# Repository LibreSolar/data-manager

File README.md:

# Data Manager for Libre Solar devices

 Prototype built, development and testing ongoing (especially firmware).

Schematic: [PDF file](data-manager.pdf)

Firmware repository: [LibreSolar/data-manager-firmware](https://github.com/LibreSolar/data-manager-firmware)

## Features

- ESP32 WROOM board for WiFi and Bluetooth connection
- USB Micro-B power supply and debug serial
- microSD card slot
- LS.one interface (UART serial)
- LS.bus interface (CAN)
- Suitable housing: Hammond Mfg. 1591XXAFLBK

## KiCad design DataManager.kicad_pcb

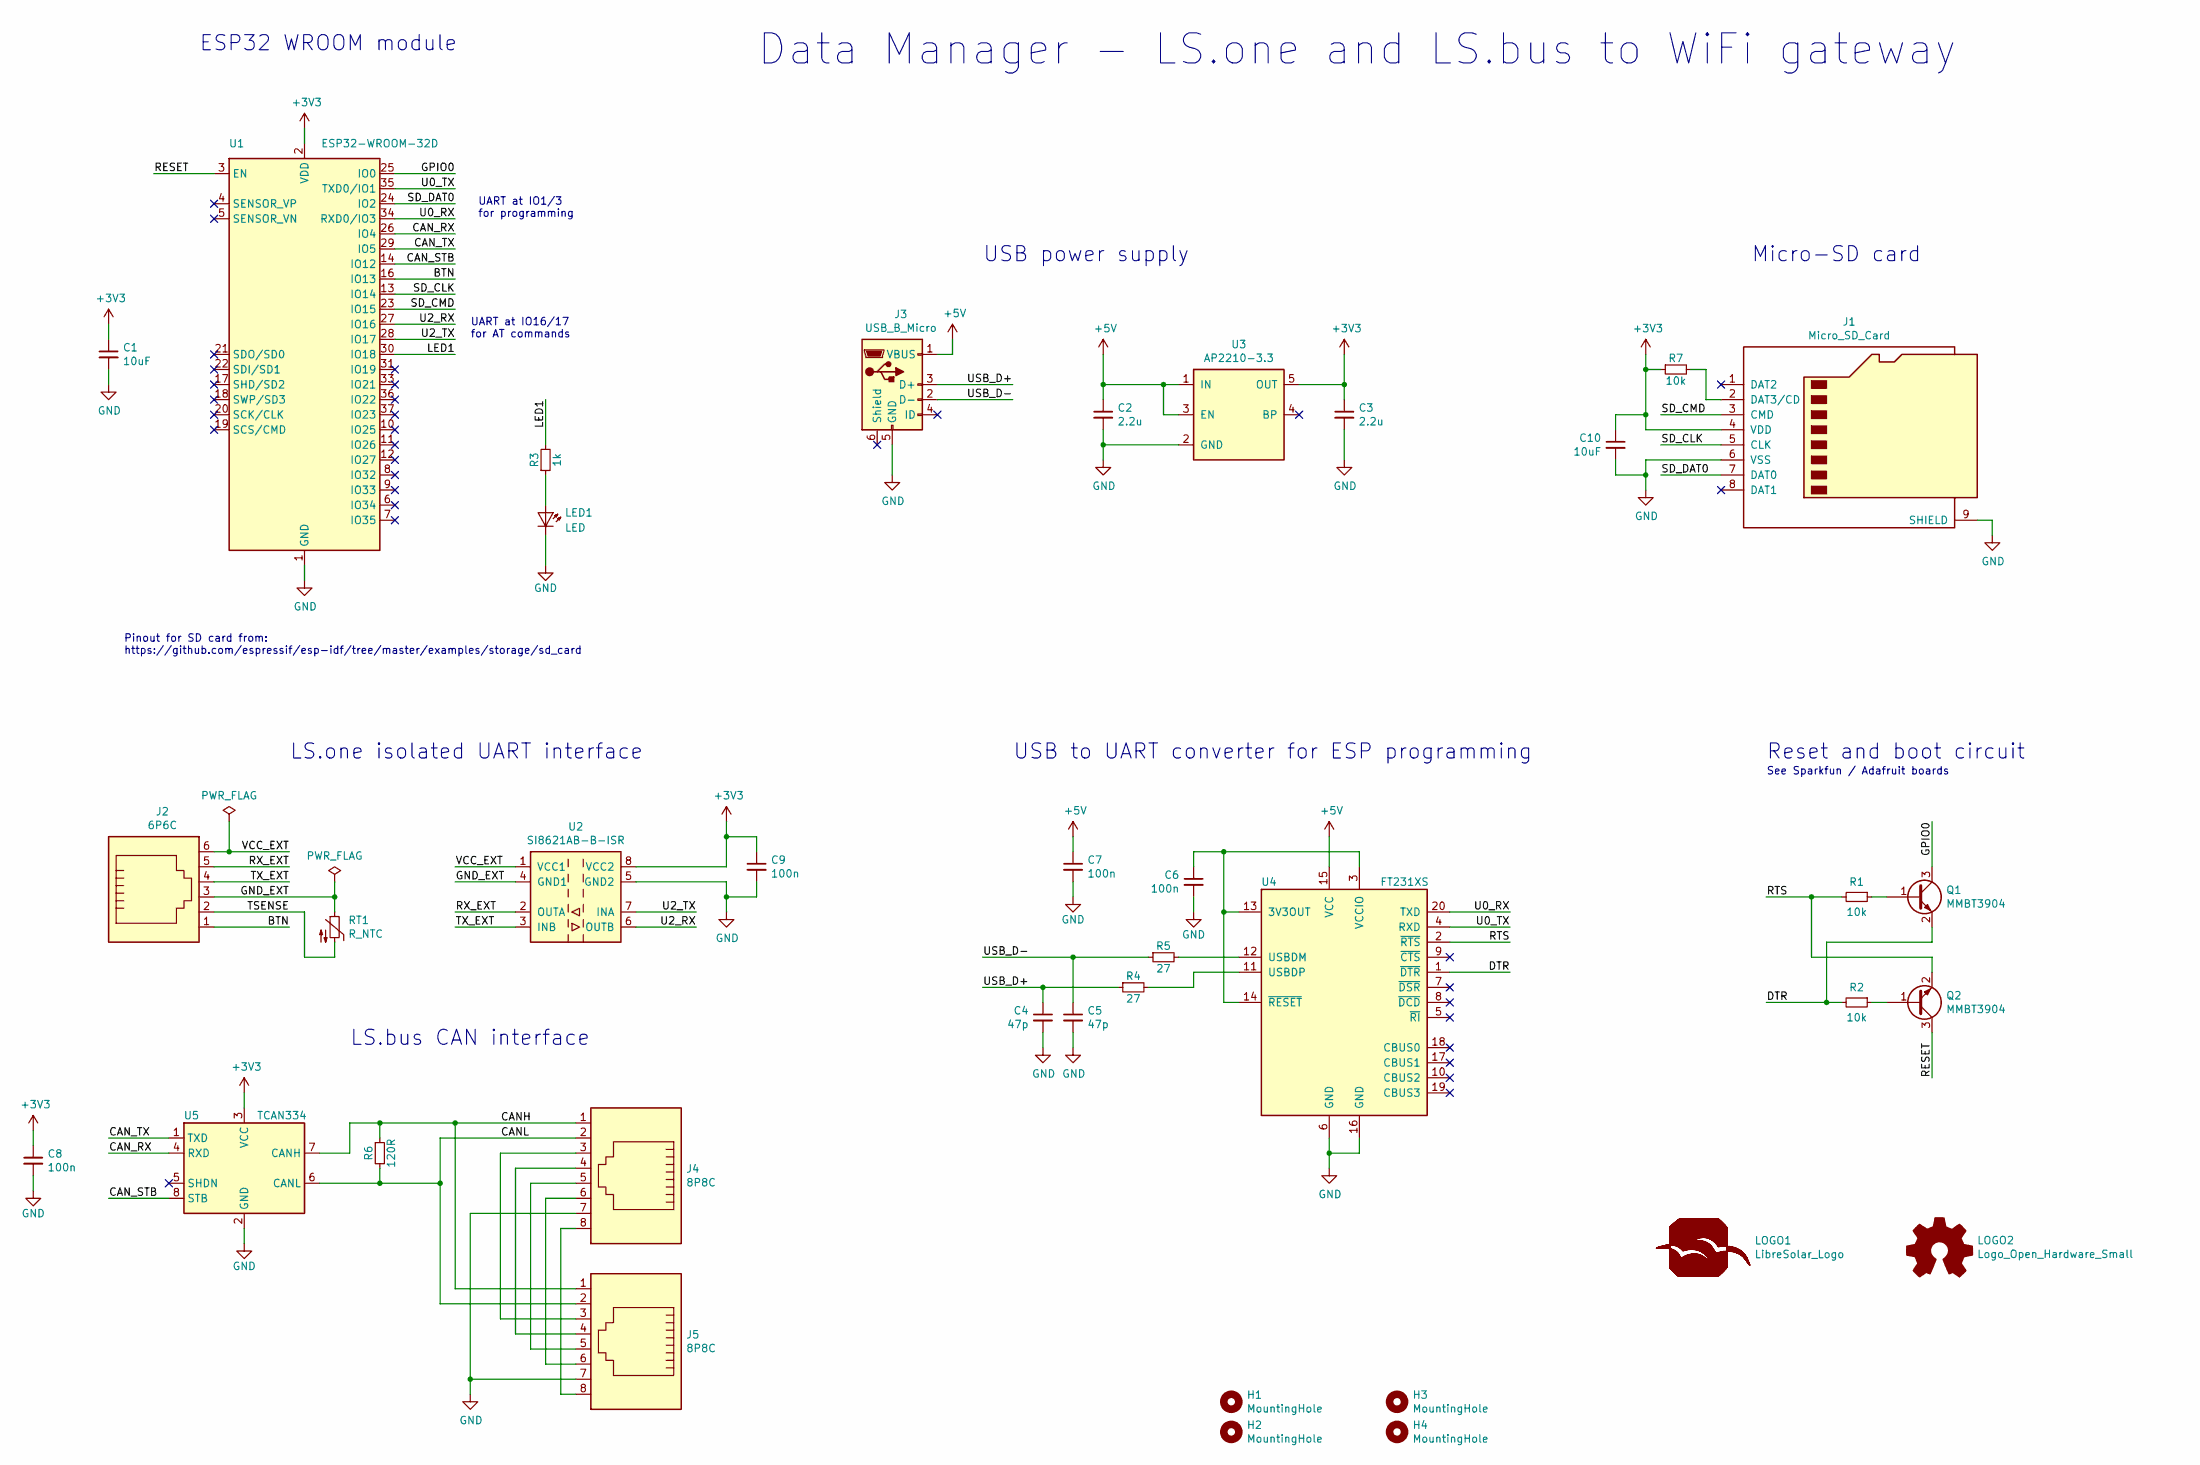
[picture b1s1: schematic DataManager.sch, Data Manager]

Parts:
C1, C10: 10uF; C_0805_2012; PartNumber GRM21BR61C106KE15L
C2, C3: 2.2u; C_0603_1608
C4, C5: 47p; C_0603_1608
C6, C7, C8, C9: 100n; C_0603_1608
H1, H2, H3, H4: MountingHole; MountingHole_2.5mm
J1: Micro_SD_Card; microSD_HC_Hirose_DM3D-SF; PartNumber DM3D-SF
J2: 6P6C; RJ12_RJ25_6P6C_Amphenol_54601; PartNumber 54601-906WPLF
J3: USB_B_Micro; USB_Micro-B_10103594-0001LF
J4, J5: 8P8C; RJ45_8P8C
LED1: LED; LED_0603_1608Metric
LOGO1: LibreSolar_Logo; LIBRESOLAR_LOGO
LOGO2: Logo_Open_Hardware_Small; OSHW-Logo_5.7x6mm_SilkScreen
Q1, Q2: MMBT3904; SOT-23
R1, R2, R7: 10k; R_0603_1608; PartNumber RC0603FR-0710KL
R3: 1k; R_0603_1608; PartNumber RC0603FR-071KL
R4, R5: 27; R_0603_1608; PartNumber RC0603FR-0727RL
R6: 120R; R_1206_3216; PartNumber RC1206FR-07120RL
RT1: R_NTC; R_0603_1608
U1: ESP32-WROOM-32D; ESP32-WROOM-32
U2: SI8621AB-B-ISR; SOIC-8_3.9x4.9mm_P1.27mm
U3: AP2210-3.3; SOT-23-5
U4: FT231XS; SSOP-20_3.9x8.7mm_P0.635mm
U5: TCAN334; SOIC-8_3.9x4.9mm_Pitch1.27mm

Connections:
+3V3: C1.1, C3.1, C8.1, C9.1, C10.1, J1.4 (VDD), R7.1, U1.2 (VDD), U2.8 (VCC2), U3.5 (OUT), U5.3 (VCC)
+5V: C2.1, C7.1, J3.1 (VBUS), U3.1 (IN), U3.3 (EN), U4.15 (VCC)
/BTN: J2.1, U1.16 (IO13)
/CANH: J4.1, J5.1, R6.1, U5.7 (CANH)
/CANL: J4.2, J5.2, R6.2, U5.6 (CANL)
/CAN_RX: U1.26 (IO4), U5.4 (RXD)
/CAN_STB: U1.14 (IO12), U5.8 (STB)
/CAN_TX: U1.29 (IO5), U5.1 (TXD)
/DTR: Q1.2 (E), R2.2, U4.1 (~DTR)
/GND_EXT: J2.3, RT1.1, U2.4 (GND1)
/GPIO0: Q1.3 (C), U1.25 (IO0)
/LED1: R3.2, U1.30 (IO18)
/RESET: Q2.3 (C), U1.3 (EN)
/RTS: Q2.2 (E), R1.2, U4.2 (~RTS)
/RX_EXT: J2.5, U2.2 (OUTA)
/SD_CLK: J1.5 (CLK), U1.13 (IO14)
/SD_CMD: J1.3 (CMD), U1.23 (IO15)
/SD_DAT0: J1.7 (DAT0), U1.24 (IO2)
/TSENSE: J2.2, RT1.2
/TX_EXT: J2.4, U2.3 (INB)
/U0_RX: U1.34 (RXD0/IO3), U4.20 (TXD)
/U0_TX: U1.35 (TXD0/IO1), U4.4 (RXD)
/U2_RX: U1.27 (IO16), U2.6 (OUTB)
/U2_TX: U1.28 (IO17), U2.7 (INA)
/USB_D+: C4.1, J3.3 (D+), R4.1
/USB_D-: C5.1, J3.2 (D-), R5.1
/VCC_EXT: J2.6, U2.1 (VCC1)
GND: C1.2, C2.2, C3.2, C4.2, C5.2, C6.2, C7.2, C8.2, C9.2, C10.2, J1.6 (VSS), J1.9 (SHIELD), J3.5 (GND), J4.7, J5.7, LED1.1 (K), U1.1 (GND), U1.15 (GND), U1.38 (GND), U2.5 (GND2), U3.2 (GND), U4.6 (GND), U4.16 (GND), U5.2 (GND)
unnamed: C6.1, U4.3 (VCCIO), U4.13 (3V3OUT), U4.14 (~RESET)
unnamed: J1.2 (DAT3/CD), R7.2
unnamed: J4.3, J5.3
unnamed: J4.4, J5.4
unnamed: J4.5, J5.5
unnamed: J4.6, J5.6
unnamed: J4.8, J5.8
unnamed: LED1.2 (A), R3.1
unnamed: Q1.1 (B), R1.1
unnamed: Q2.1 (B), R2.1
unnamed: R4.2, U4.11 (USBDP)
unnamed: R5.2, U4.12 (USBDM)

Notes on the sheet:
UART at IO1/3 for programming
UART at IO16/17 for AT commands
See Sparkfun / Adafruit boards
Reset and boot circuit
ESP32 WROOM module
Pinout for SD card from: https://github.com/espressif/esp-idf/tree/master/examples/storage/sd_card
USB power supply
LS.bus CAN interface
Micro-SD card
LS.one isolated UART interface
USB to UART converter for ESP programming
Data Manager - LS.one and LS.bus to WiFi gateway

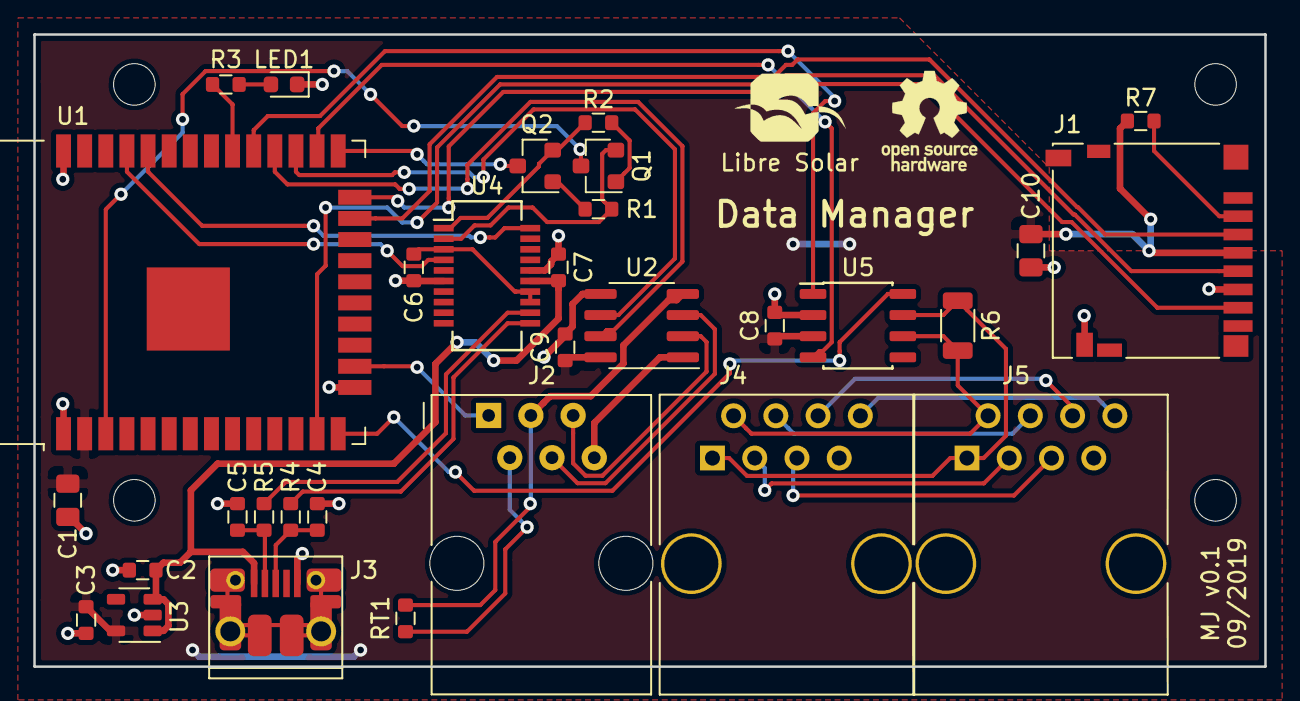
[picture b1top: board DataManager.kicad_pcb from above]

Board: 2 copper layers, 74.0 x 38.0 mm, 37 parts (0 on the bottom side), 40 nets.

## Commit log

2019-10-17 Initial commit of v0.1 board
2019-12-23 Board v0.2: Errors fixed
    - Pull-up resistor on reset pin
    - LS.one (serial) pinout fixed (reversed)
    - Isolator U2 RX/TX pinout fixed
    - PCB mounting hole diameter enlarged to 3 mm
2019-12-23 Files renamed and PDF schematic added
